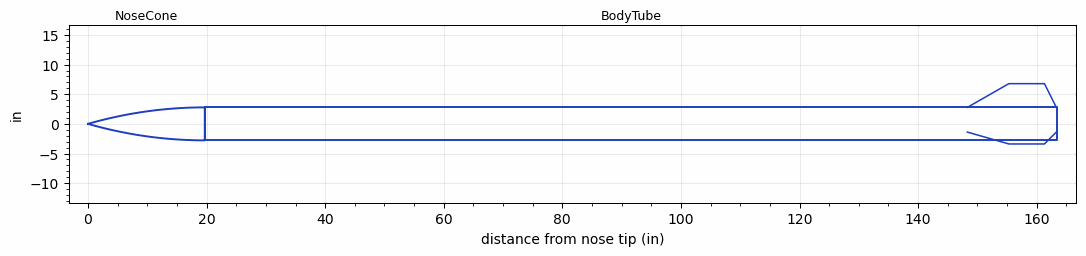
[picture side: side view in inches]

<RASAeroDocument>
 <FileVersion>2</FileVersion>
 <RocketDesign>
  <NoseCone>
   <Length>19.69</Length>
   <Diameter>5.563</Diameter>
   <Shape>Tangent Ogive</Shape>
   <Location>0</Location>
  </NoseCone>
  <BodyTube>
   <Length>143.7008</Length>
   <Diameter>5.563</Diameter>
   <RailGuideDiameter>0.66</RailGuideDiameter>
   <RailGuideHeight>0.385</RailGuideHeight>
   <Location>19.69</Location>
   <Fin>
    <Count>3</Count>
    <Chord>15</Chord>
    <Span>4</Span>
    <SweepDistance>7</SweepDistance>
    <TipChord>6</TipChord>
    <Thickness>0.25</Thickness>
    <LERadius>0.02</LERadius>
    <Location>15.0787</Location>
    <AirfoilSection>Hexagonal</AirfoilSection>
    <FX1>0.25</FX1>
    <FX3>0.25</FX3>
   </Fin>
  </BodyTube>
  <Surface>Smooth Paint</Surface>
  <ModifiedBarrowman>True</ModifiedBarrowman>
  <Turbulence>False</Turbulence>
  <UseBooster1>False</UseBooster1>
  <UseBooster2>False</UseBooster2>
 </RocketDesign>
 <LaunchSite>
  <Altitude>0</Altitude>
  <Pressure>0</Pressure>
  <RodAngle>0</RodAngle>
  <RodLength>4</RodLength>
  <Temperature>74</Temperature>
  <WindSpeed>0</WindSpeed>
 </LaunchSite>
 <Recovery>
  <Altitude1>1000</Altitude1>
  <Altitude2>1000</Altitude2>
  <DeviceType1>None</DeviceType1>
  <DeviceType2>None</DeviceType2>
  <Event1>False</Event1>
  <Event2>False</Event2>
  <Size1>1</Size1>
  <Size2>1</Size2>
  <EventType1>None</EventType1>
  <EventType2>None</EventType2>
  <CD1>1.33</CD1>
  <CD2>1.33</CD2>
 </Recovery>
 <SimulationList>
  <Simulation>
   <SustainerEngine>hybrid  (UVR)</SustainerEngine>
   <SustainerLaunchWt>165.4</SustainerLaunchWt>
   <SustainerNozzleDiameter>4.188</SustainerNozzleDiameter>
   <SustainerCG>108</SustainerCG>
   <SustainerIgnitionDelay>0</SustainerIgnitionDelay>
   <Booster1SeparationDelay>0</Booster1SeparationDelay>
   <Booster1IgnitionDelay>0</Booster1IgnitionDelay>
   <IncludeBooster1>False</IncludeBooster1>
   <Booster2Delay>0</Booster2Delay>
   <IncludeBooster2>False</IncludeBooster2>
   <TimetoApogee>44.28857</TimetoApogee>
   <MaxAltitude>29272.89</MaxAltitude>
   <MaxVelocity>1408.623</MaxVelocity>
  </Simulation>
 </SimulationList>
</RASAeroDocument>
